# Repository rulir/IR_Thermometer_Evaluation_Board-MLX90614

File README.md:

SparkFun IR Thermometer Evaluation Board - MLX90614
========================================

[*SparkFun IR Thermometer Evaluation Board - MLX90614 (SEN-10740)*](https://www.sparkfun.com/products/10740)

The MLX9061 sensor is a high precision, small size, single zone IR thermometer with an optional SMBus (two-wire) or PWM interface. 
The ATMega328 comes with demo code that gives a temperature readout in degrees F at 38400bps. 
You can use a 3.3V FTDI Basic to connect to the board.

Repository Contents
-------------------

* **/Firmware** - Example code 
* **/Hardware** - Eagle design files (.brd, .sch)
* **/Production** - Production panel files (.brd)
* **/Libraries** - Arduino library

Documentation
--------------
* **[SparkFun Fritzing repo](https://github.com/sparkfun/Fritzing_Parts)** - Fritzing diagrams for SparkFun products.
* **[SparkFun 3D Model repo](https://github.com/sparkfun/3D_Models)** - 3D models of SparkFun products. 

License Information
-------------------
This product is _**open source**_! 

The **hardware** is released under [Creative Commons ShareAlike 4.0 International](https://creativecommons.org/licenses/by-sa/4.0/).

The **code** is beerware; if you see me (or any other SparkFun employee) at the local, and you've found our code helpful, please buy us a round!

Please use, reuse, and modify these files as you see fit. Please maintain attribution to SparkFun Electronics and release anything derivative under the same license.

Distributed as-is; no warranty is given.

- Your friends at SparkFun.

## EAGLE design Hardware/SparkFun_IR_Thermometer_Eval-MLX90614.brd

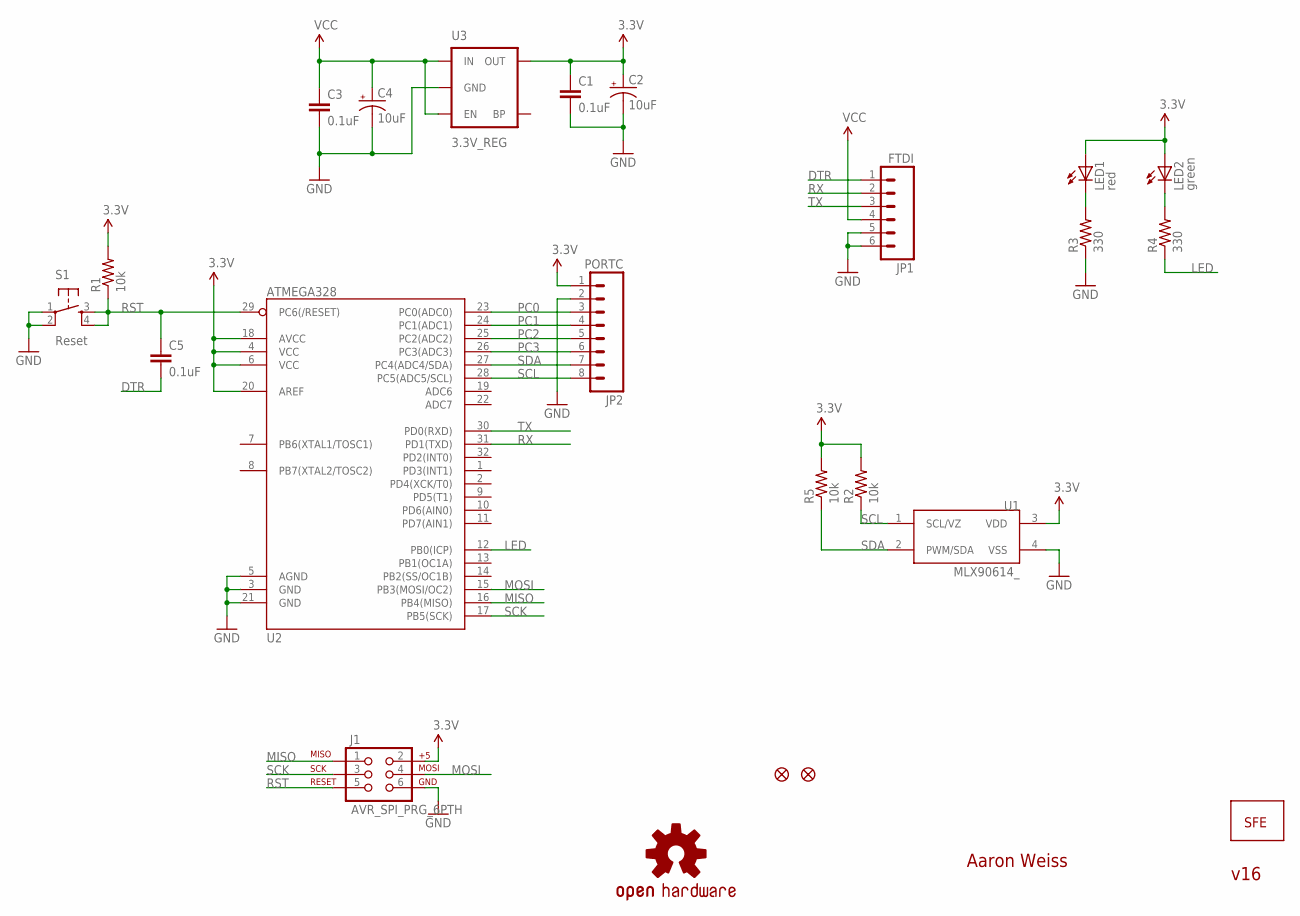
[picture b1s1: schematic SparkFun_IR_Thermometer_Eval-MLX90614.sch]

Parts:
C1, C3, C5: 0.1uF; 0402-CAP
C2, C4: 10uF; EIA3216
J1: AVR_SPI_PRG_6PTH; 2X3
JP1: FTDI; 1X06
JP2: PORTC; 1X08
JP3, JP5: FIDUCIAL1X2.5; FIDUCIAL-1X2.5
JP4: LOGO-SFESK; SFE-LOGO-FLAME
LED1: red; LED-0603
LED2: green; LED-0603
R1, R2, R5: 10k; 0402-RES
R3, R4: 330; 0402-RES
S1: Reset; TACTILE_SWITCH_SMD
U1: MLX90614_; TO-39
U2: ATMEGA328; TQFP32-08
U3: 3.3V_REG; SOT23-5
U$1: OSHW-LOGOS; OSHW-LOGO-S

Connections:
3.3V: C1.1, C2.A (+), J1.2, JP2.1, LED1.A, LED2.A, R1.2, R2.2, R5.2, U1.3 (VDD), U2.4 (VCC), U2.6 (VCC), U2.18 (AVCC), U2.20 (AREF), U3.5 (OUT)
DTR: C5.2, JP1.1
GND: C1.2, C2.C (-), C3.2, C4.C (-), J1.6, JP1.5, JP1.6, JP2.2, R3.1, S1.1, S1.2, U1.4 (VSS), U2.3 (GND), U2.5 (AGND), U2.21 (GND), U3.2 (GND)
LED: R4.1, U2.12 (PB0(ICP))
MISO: J1.1, U2.16 (PB4(MISO))
MOSI: J1.4, U2.15 (PB3(MOSI/OC2))
unnamed: LED1.C, R3.2
unnamed: LED2.C, R4.2
PC0: JP2.3, U2.23 (PC0(ADC0))
PC1: JP2.4, U2.24 (PC1(ADC1))
PC2: JP2.5, U2.25 (PC2(ADC2))
PC3: JP2.6, U2.26 (PC3(ADC3))
RST: C5.1, J1.5, R1.1, S1.3, S1.4, U2.29 (PC6(/RESET))
RX: JP1.2, U2.31 (PD1(TXD))
SCK: J1.3, U2.17 (PB5(SCK))
SCL: JP2.8, R2.1, U1.1 (SCL/VZ), U2.28 (PC5(ADC5/SCL))
SDA: JP2.7, R5.1, U1.2 (PWM/SDA), U2.27 (PC4(ADC4/SDA))
TX: JP1.3, U2.30 (PD0(RXD))
VCC: C3.1, C4.A (+), JP1.4, U3.1 (IN), U3.3 (EN)

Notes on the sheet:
v16
Aaron Weiss

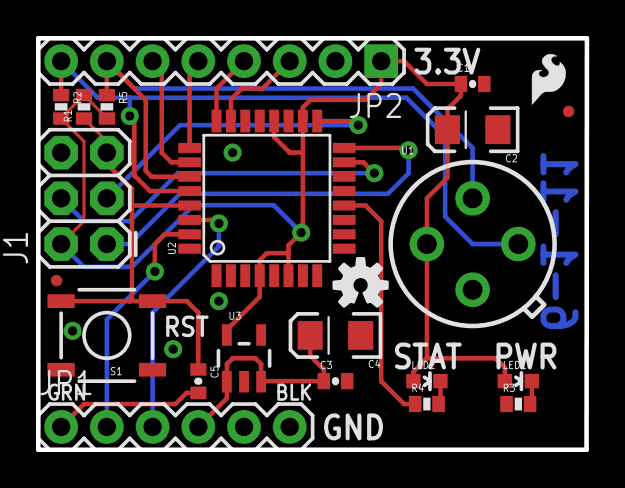
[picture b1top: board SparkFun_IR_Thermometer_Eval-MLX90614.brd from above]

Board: 2 copper layers, 30.5 x 22.9 mm, 23 parts (0 on the bottom side), 19 nets.

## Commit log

2015-05-07 Adding hardware, simple sketch, modifying original code format
2015-10-29 Squashed 'Libraries/Arduino/' content from commit 685d598
    git-subtree-dir: Libraries/Arduino
    git-subtree-split: 685d5982f8ea6b3f40d49d6d1de3f3648623114a
2015-10-29 Adding README.md to Libraries directory.
2015-10-29 Adding Libraries to repo contents section.
2016-03-30 speed changes
